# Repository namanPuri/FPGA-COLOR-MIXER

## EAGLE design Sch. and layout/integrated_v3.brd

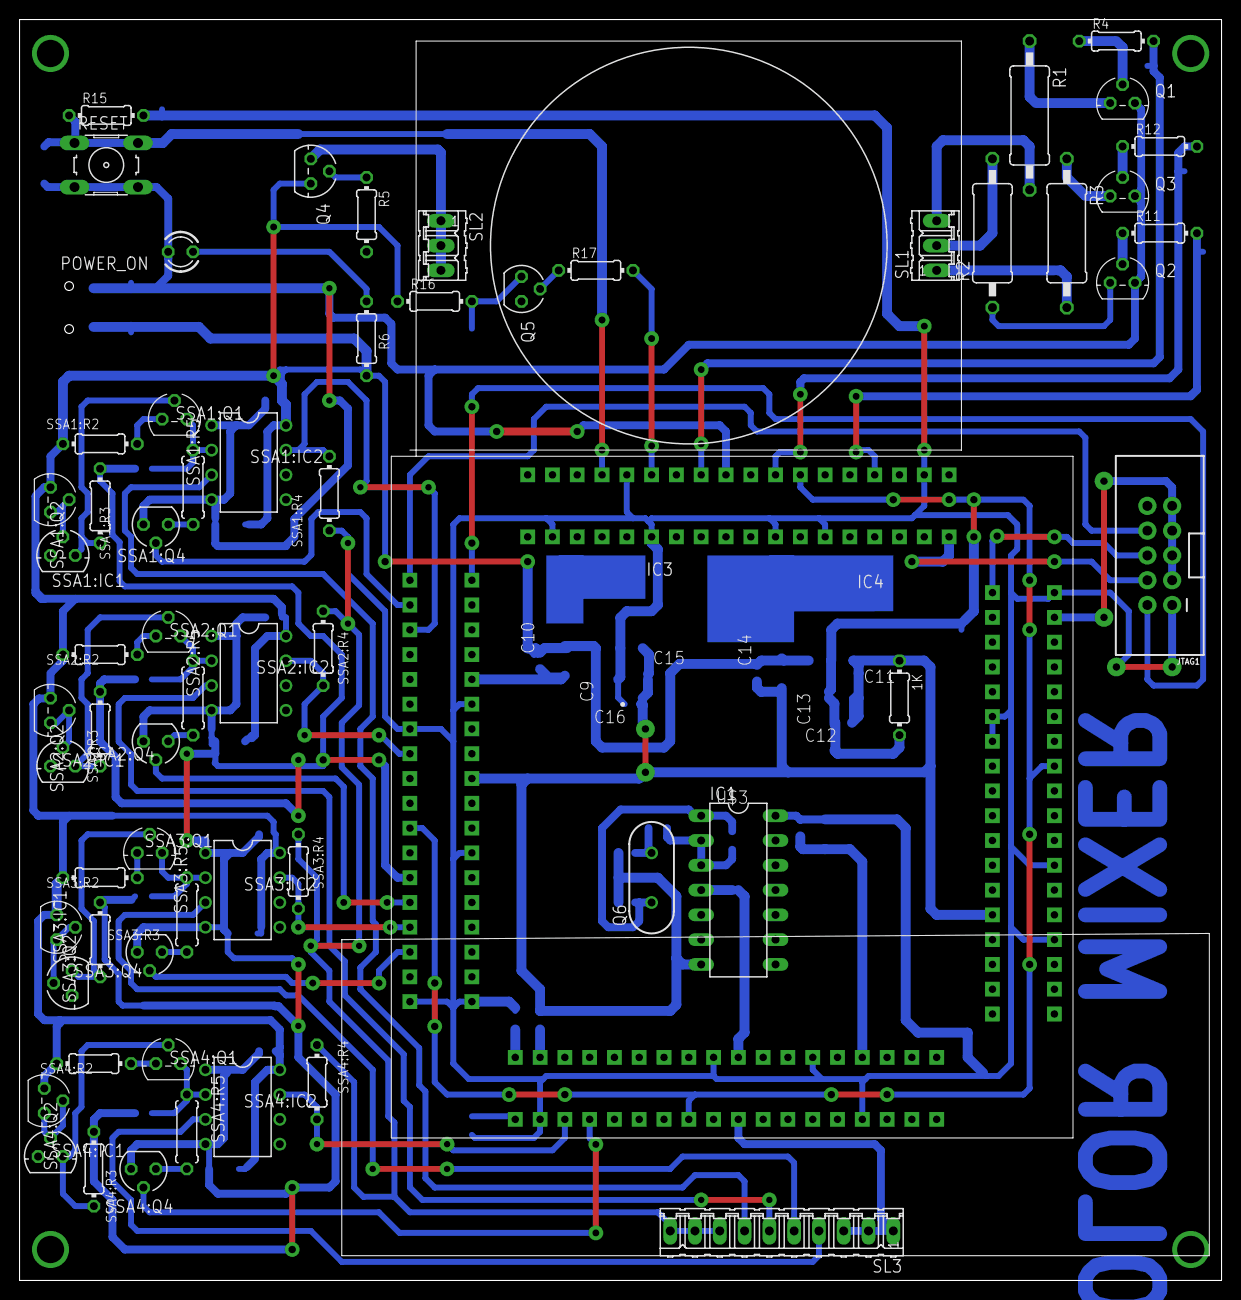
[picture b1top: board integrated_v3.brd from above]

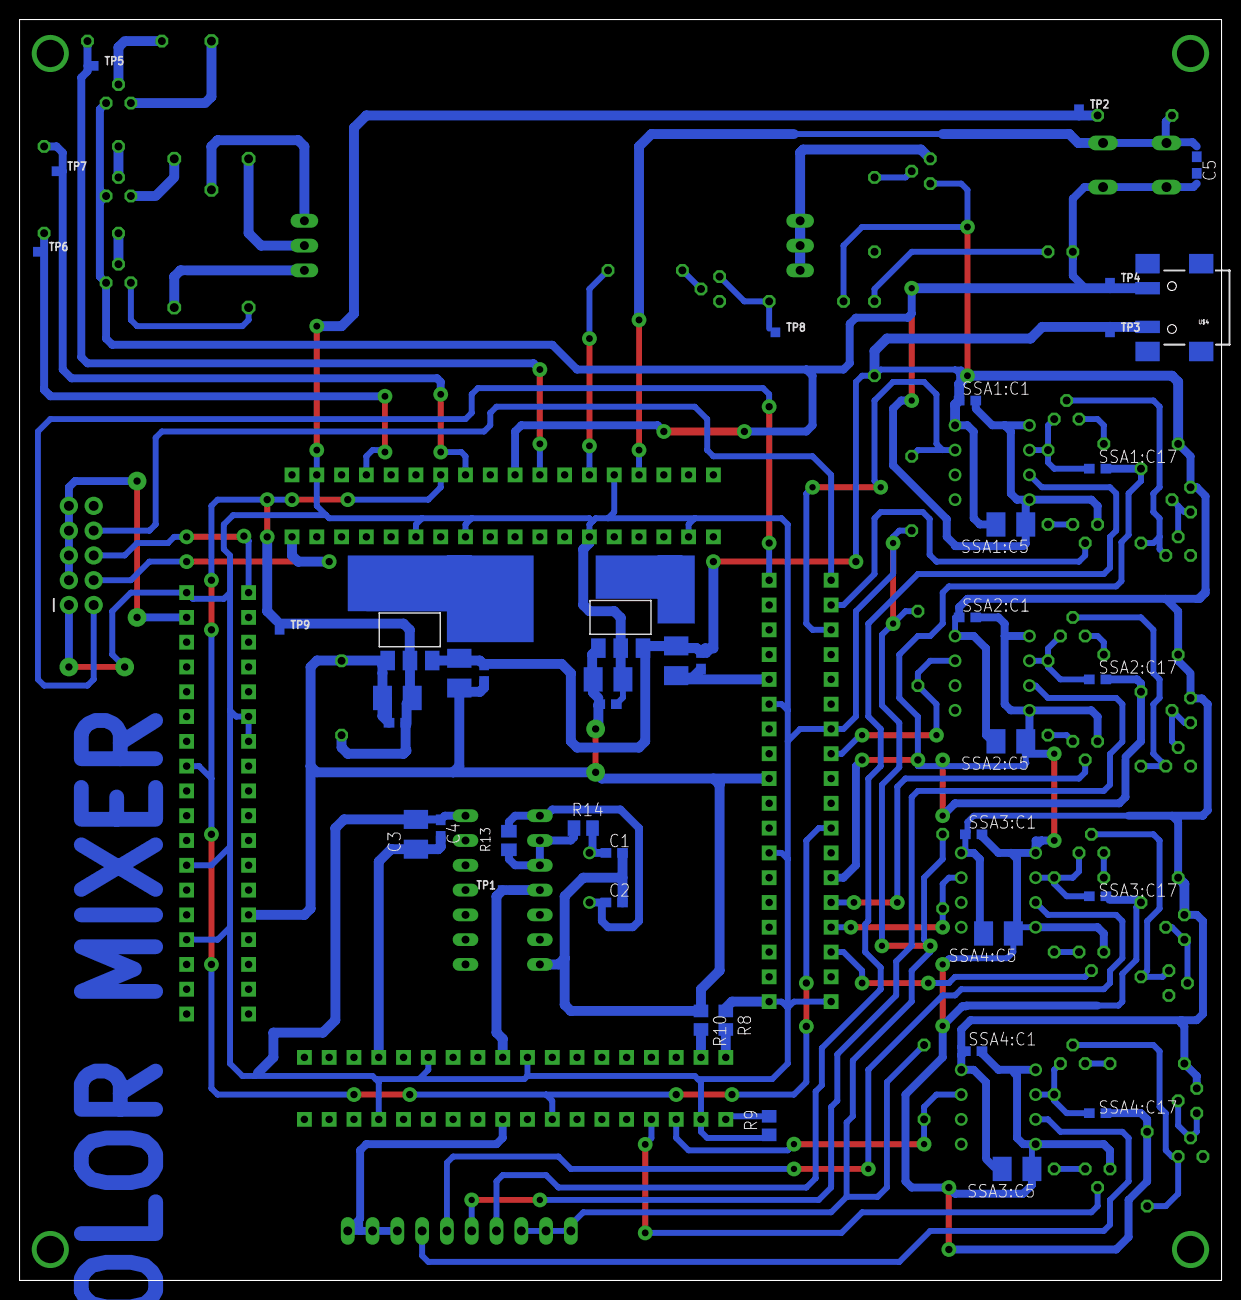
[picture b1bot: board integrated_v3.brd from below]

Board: 2 copper layers, 123.2 x 129.2 mm, 104 parts (42 on the bottom side), 66 nets.

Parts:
1K: 0204/7
C1: 22P; C0603
C2: 10P; C0603
C3, C9, C11, C13, C15: 10u; B/3528-21R
C4, C5, C10, C12, C14, C16: 0.1u; C0603
IC1: 74HC14N; DIL14
IC3, IC4: REG1117; SOT223
JTAG1: 2X5-SHROUDED_LOCK_PROPER
POWER_ON: LED3MM
Q1, Q2, Q3: BC337; TO92
Q4: BC327; TO92
Q5: BC547; SOT54A
Q6: 12MHZ; HC49US
R1, R2: 22; 0411/15
R3: 15; 0411/15
R4, R5, R11, R12, R17: 1k; 0204/7
R6: 4.7k; 0204/7
R8, R9, R10: 330; R0805
R13: 1M; M0805
R14: 100; M0805
R15: 330; 0204/7
R16: 10k; 0204/7
RESET: 10xx; B3F-10XX
SL1, SL2: 03P
SL3: 10P
SSA1:C1, SSA1:C17, SSA2:C1, SSA2:C17, SSA3:C1, SSA3:C17, SSA4:C1, SSA4:C17: 0.1u; C0603
SSA1:C5, SSA2:C5, SSA3:C5, SSA4:C5: 10u; B/3528-21R
SSA1:IC1, SSA2:IC1, SSA3:IC1, SSA4:IC1: LM336LP; TO92
SSA1:IC2, SSA2:IC2, SSA3:IC2, SSA4:IC2: LM311N; DIL08
SSA1:Q1, SSA1:Q2, SSA2:Q1, SSA2:Q2, SSA3:Q1, SSA3:Q2, SSA4:Q1, SSA4:Q2: BC557; TO92
SSA1:Q4, SSA2:Q4, SSA3:Q4, SSA4:Q4: BS170; SOT54E
SSA1:R2, SSA2:R2, SSA3:R2, SSA4:R2: 1.5k; 0204/7
SSA1:R3, SSA2:R3, SSA3:R3, SSA4:R3: 2k; 0204/7
SSA1:R4, SSA2:R4, SSA3:R4, SSA4:R4: 1k; 0204/7
SSA1:R5, SSA2:R5, SSA3:R5, SSA4:R5: 10; 0207/7
TP1, TP2, TP3, TP4, TP5, TP6, TP7, TP8, TP9: TESTPOINT_TPS-SMD-10SN; TESTPOINT_SMD-10SN
U$3: 144_BOB
U$4: USB(POWER)

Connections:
+1.2V: 1K.2, C11.+, C12.1, IC4.2, TP9.TP, U$3.22, U$3.52, U$3.94, U$3.122
+3V3: C3.+, C4.1, C15.+, C16.1, IC1.14, IC3.2, JTAG1.1, R8.1, R9.1, R15.2, SL3.8, SL3.9, SL3.10, SSA1:R4.2, SSA2:R4.2, SSA3:R4.2, SSA4:R4.2, TP2.TP, U$3.11, U$3.14, U$3.23, U$3.35, U$3.36, U$3.40, U$3.53, U$3.61, U$3.66, U$3.80, U$3.86, U$3.95, U$3.97, U$3.108, U$3.112, U$3.119, U$3.123, U$3.133, U$3.136, U$3.141
+5V: C9.+, C10.1, C13.+, C14.1, IC3.3, IC4.3, Q4.1, R6.2, R16.1, SSA1:C1.1, SSA1:C5.+, SSA1:IC2.8, SSA1:Q2.3, SSA1:R2.2, SSA2:C1.1, SSA2:C5.+, SSA2:IC2.8, SSA2:Q2.3, SSA2:R2.2, SSA3:C1.1, SSA3:C5.+, SSA3:IC2.8, SSA3:Q2.3, SSA3:R2.2, SSA4:C1.1, SSA4:C5.+, SSA4:IC2.8, SSA4:Q2.3, SSA4:R2.2, TP3.TP, U$4.VBUS
ADC_B: SSA3:IC2.7, SSA3:R4.1, U$3.30
ADC_G: SSA2:IC2.7, SSA2:R4.1, U$3.16
ADC_I: SSA4:IC2.7, SSA4:R4.1, U$3.42
ADC_R: SSA1:IC2.7, SSA1:R4.1, U$3.6
BLUE: R12.2, TP7.TP, U$3.124
CLK: IC1.4, TP1.TP, U$3.55
DIS_B: SSA3:Q4.G, U$3.32
DIS_G: SSA2:Q4.G, U$3.28
DIS_I: SSA4:Q4.G, U$3.44
DIS_R: SSA1:Q4.G, U$3.4
GND: 1K.1, C1.2, C2.2, C3.-, C4.2, C5.2, C9.-, C10.2, C11.-, C12.2, C13.-, C14.2, C15.-, C16.2, IC1.7, IC3.1, IC4.1, JTAG1.3, JTAG1.5, JTAG1.7, JTAG1.9, POWER_ON.K, Q1.1, Q2.1, Q3.1, Q5.E, R10.1, RESET.3, RESET.4, SL3.1, SL3.2, SL3.3, SSA1:C1.2, SSA1:C5.-, SSA1:C17.2, SSA1:IC2.1, SSA1:IC2.4, SSA1:Q4.S, SSA1:R3.1, SSA2:C1.2, SSA2:C5.-, SSA2:C17.2, SSA2:IC2.1, SSA2:IC2.4, SSA2:Q4.S, SSA2:R3.1, SSA3:C1.2, SSA3:C5.-, SSA3:C17.2, SSA3:IC2.1, SSA3:IC2.4, SSA3:Q4.S, SSA3:R3.1, SSA4:C1.2, SSA4:C5.-, SSA4:C17.2, SSA4:IC2.1, SSA4:IC2.4, SSA4:Q4.S, SSA4:R3.1, TP4.TP, U$3.9, U$3.17, U$3.26, U$3.34, U$3.56, U$3.65, U$3.81, U$3.89, U$3.100, U$3.106, U$3.118, U$3.128, U$3.137, U$4.GND
GREEN: R4.2, TP5.TP, U$3.130
INTENSITY: R17.2, U$3.134
INTENSITY5: Q5.C, R5.2, R16.2, TP8.TP
unnamed: Q1.3, R1.1
unnamed: R1.2, SL1.3
unnamed: Q2.3, R2.1
unnamed: C2.1, IC1.1, Q6.1, R13.2
unnamed: Q5.B, R17.1
unnamed: Q3.3, R3.1
unnamed: R3.2, SL1.1
unnamed: Q1.2, R4.1
unnamed: Q2.2, R11.1
unnamed: Q3.2, R12.1
unnamed: R2.2, SL1.2
unnamed: IC1.2, IC1.3, R13.1, R14.1
unnamed: C1.1, Q6.2, R14.2
unnamed: Q4.2, R5.1
unnamed: Q4.3, SL2.1, SL2.2, SL2.3
unnamed: POWER_ON.A, R6.1
unnamed: R8.2, U$3.37
unnamed: R9.2, U$3.38
unnamed: R10.2, U$3.39
POT_B: SL3.5, SSA3:IC2.3
POT_G: SL3.6, SSA2:IC2.3
POT_I: SL3.4, SSA4:IC2.3
POT_R: SL3.7, SSA1:IC2.3
RED: R11.2, TP6.TP, U$3.116
RESET: C5.1, R15.1, RESET.1, RESET.2, U$3.138
SSA1:COMP: SSA1:C17.1, SSA1:IC2.2, SSA1:Q1.1, SSA1:R5.2
SSA1:N$2: SSA1:Q1.3, SSA1:R2.1
SSA1:N$3: SSA1:IC1.2, SSA1:Q2.1, SSA1:Q2.2
SSA1:N$4: SSA1:IC1.3, SSA1:Q1.2, SSA1:R3.2
SSA1:N$5: SSA1:Q4.D, SSA1:R5.1
SSA2:COMP: SSA2:C17.1, SSA2:IC2.2, SSA2:Q1.1, SSA2:R5.2
SSA2:N$2: SSA2:Q1.3, SSA2:R2.1
SSA2:N$3: SSA2:IC1.2, SSA2:Q2.1, SSA2:Q2.2
SSA2:N$4: SSA2:IC1.3, SSA2:Q1.2, SSA2:R3.2
SSA2:N$5: SSA2:Q4.D, SSA2:R5.1
SSA3:COMP: SSA3:C17.1, SSA3:IC2.2, SSA3:Q1.1, SSA3:R5.2
SSA3:N$2: SSA3:Q1.3, SSA3:R2.1
SSA3:N$3: SSA3:IC1.2, SSA3:Q2.1, SSA3:Q2.2
SSA3:N$4: SSA3:IC1.3, SSA3:Q1.2, SSA3:R3.2
SSA3:N$5: SSA3:Q4.D, SSA3:R5.1
SSA4:COMP: SSA4:C17.1, SSA4:IC2.2, SSA4:Q1.1, SSA4:R5.2
SSA4:N$2: SSA4:Q1.3, SSA4:R2.1
SSA4:N$3: SSA4:IC1.2, SSA4:Q2.1, SSA4:Q2.2
SSA4:N$4: SSA4:IC1.3, SSA4:Q1.2, SSA4:R3.2
SSA4:N$5: SSA4:Q4.D, SSA4:R5.1
TCK: JTAG1.4, U$3.109
TDI: JTAG1.8, U$3.2
TDO: JTAG1.6, U$3.107
TMS: JTAG1.2, U$3.1

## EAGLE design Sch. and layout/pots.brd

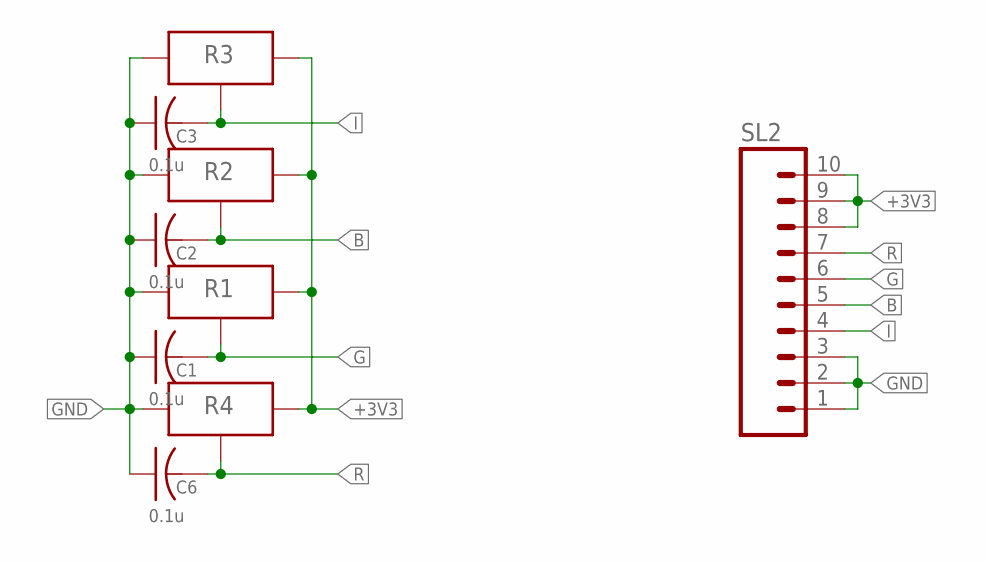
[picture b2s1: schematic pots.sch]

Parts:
C1, C2, C3, C6: 0.1u; C0603
R1, R2, R3, R4: POTNORMAL; RJ9W
SL2: M10; 10P

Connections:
+3V3: R1.A, R2.A, R3.A, R4.A, SL2.8, SL2.9, SL2.10
B: C2.2, R2.S, SL2.5
G: C1.2, R1.S, SL2.6
GND: C1.1, C2.1, C3.1, C6.1, R1.E, R2.E, R3.E, R4.E, SL2.1, SL2.2, SL2.3
I: C3.2, R3.S, SL2.4
R: C6.2, R4.S, SL2.7

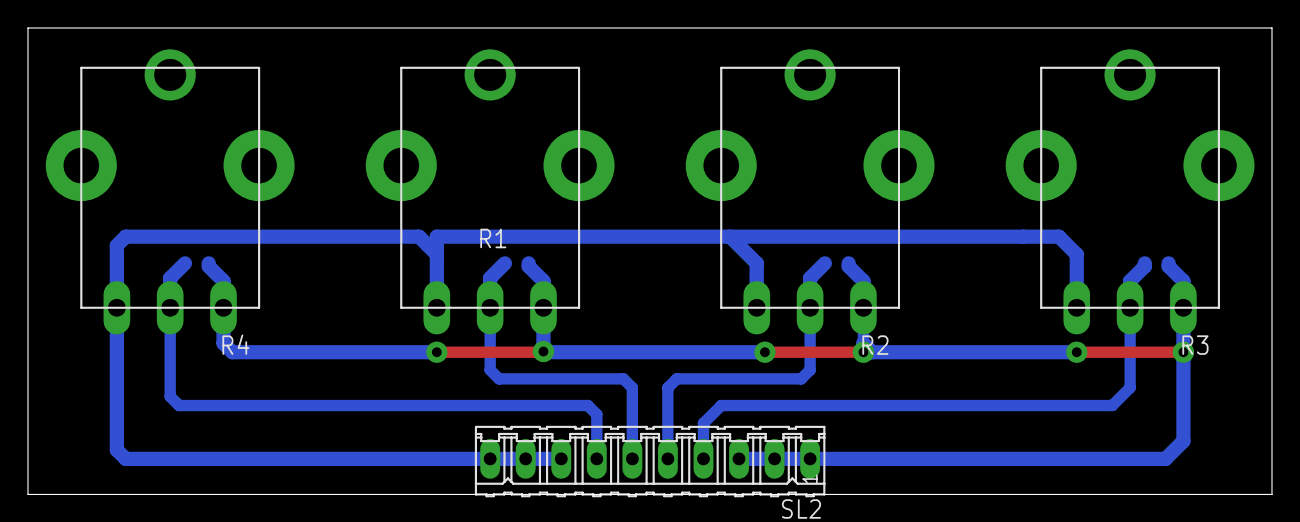
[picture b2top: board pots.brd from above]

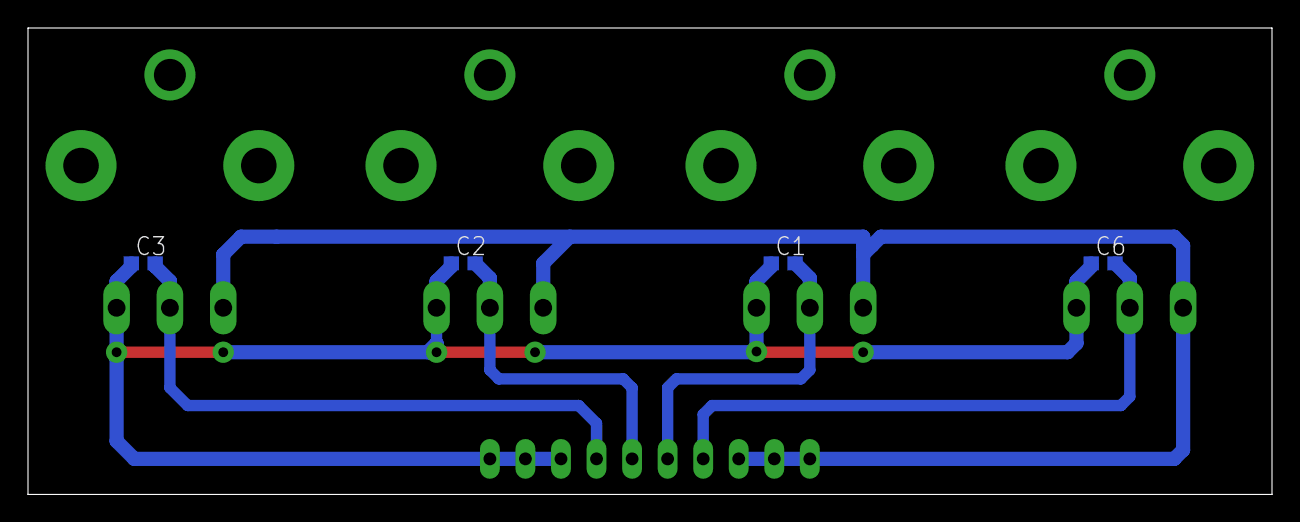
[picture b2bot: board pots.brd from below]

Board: 2 copper layers, 88.9 x 33.3 mm, 9 parts (4 on the bottom side), 6 nets.

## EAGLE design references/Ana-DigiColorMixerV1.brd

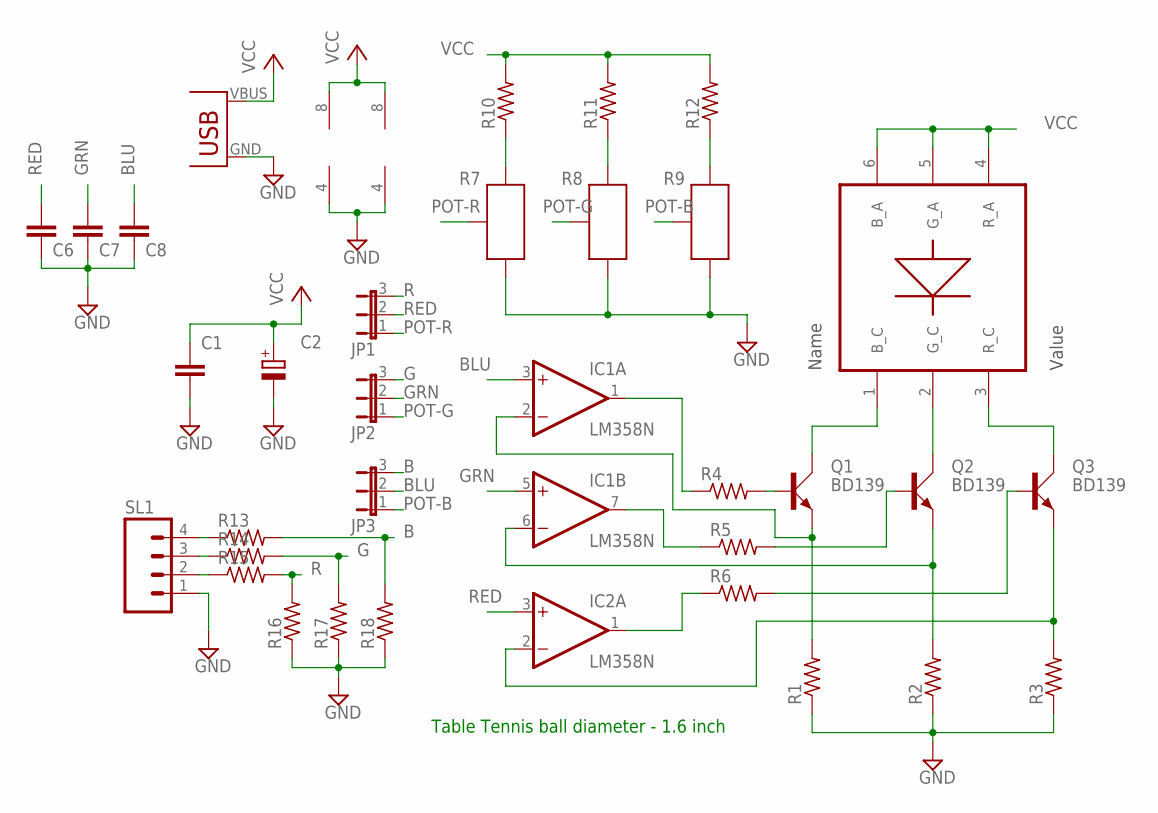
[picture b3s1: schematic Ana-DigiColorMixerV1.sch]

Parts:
C1, C6, C7, C8: 0.1uf; C025-024X044
C2: 100uf; E3,5-8
IC1, IC2: LM358N; DIL08
JP1, JP2, JP3: JP2E; JP2
Q1, Q2, Q3: BD139; TO126AV
R1: 4.7; 0411/15
R2, R3: R-US_0411/15; 0411/15
R4, R5, R6, R10, R11, R12, R13, R14, R15, R16, R17, R18: R-US_0204/7; 0204/7
R7, R8, R9: POTNORMAL; RJ9W
SL1: M04; 04P
U$1: RGB_SMD_3W; RGB_SMD_6PIN
U$2: USB(POWER)

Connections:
3V3: R9.E, R12.1
B: JP3.3, R13.2, R18.2
BLU: C8.1, IC1.3 (+IN), JP3.2
G: JP2.3, R14.2, R17.2
GND: C1.2, C2.-, C6.2, C7.2, C8.2, IC1.4 (V-), IC2.4 (V-), R1.1, R2.1, R3.1, R7.A, R8.A, R9.A, R16.1, R17.1, R18.1, SL1.1, U$2.GND
GRN: C7.1, IC1.5 (+IN), JP2.2
unnamed: Q1.C, U$1.1 (B_C)
unnamed: Q2.C, U$1.2 (G_C)
unnamed: Q3.C, U$1.3 (R_C)
unnamed: Q1.B, R4.2
unnamed: Q2.B, R5.2
unnamed: Q3.B, R6.2
unnamed: IC1.6 (-IN), Q2.E, R2.2
unnamed: R13.1, SL1.4
unnamed: IC1.1 (OUT), R4.1
unnamed: IC1.7 (OUT), R5.1
unnamed: IC2.1 (OUT), R6.1
unnamed: R14.1, SL1.3
unnamed: R15.1, SL1.2
unnamed: R7.E, R10.1
unnamed: R8.E, R11.1
unnamed: IC1.2 (-IN), Q1.E, R1.2
unnamed: IC2.2 (-IN), Q3.E, R3.2
POT-B: JP3.1, R9.S
POT-G: JP2.1, R8.S
POT-R: JP1.1, R7.S
R: JP1.3, R15.2, R16.2
RED: C6.1, IC2.3 (+IN), JP1.2
VCC: C1.1, C2.+, IC1.8 (V+), IC2.8 (V+), R10.2, R11.2, R12.2, U$1.4 (R_A), U$1.5 (G_A), U$1.6 (B_A), U$2.VBUS (VCC)

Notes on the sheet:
Table Tennis ball diameter - 1.6 inch

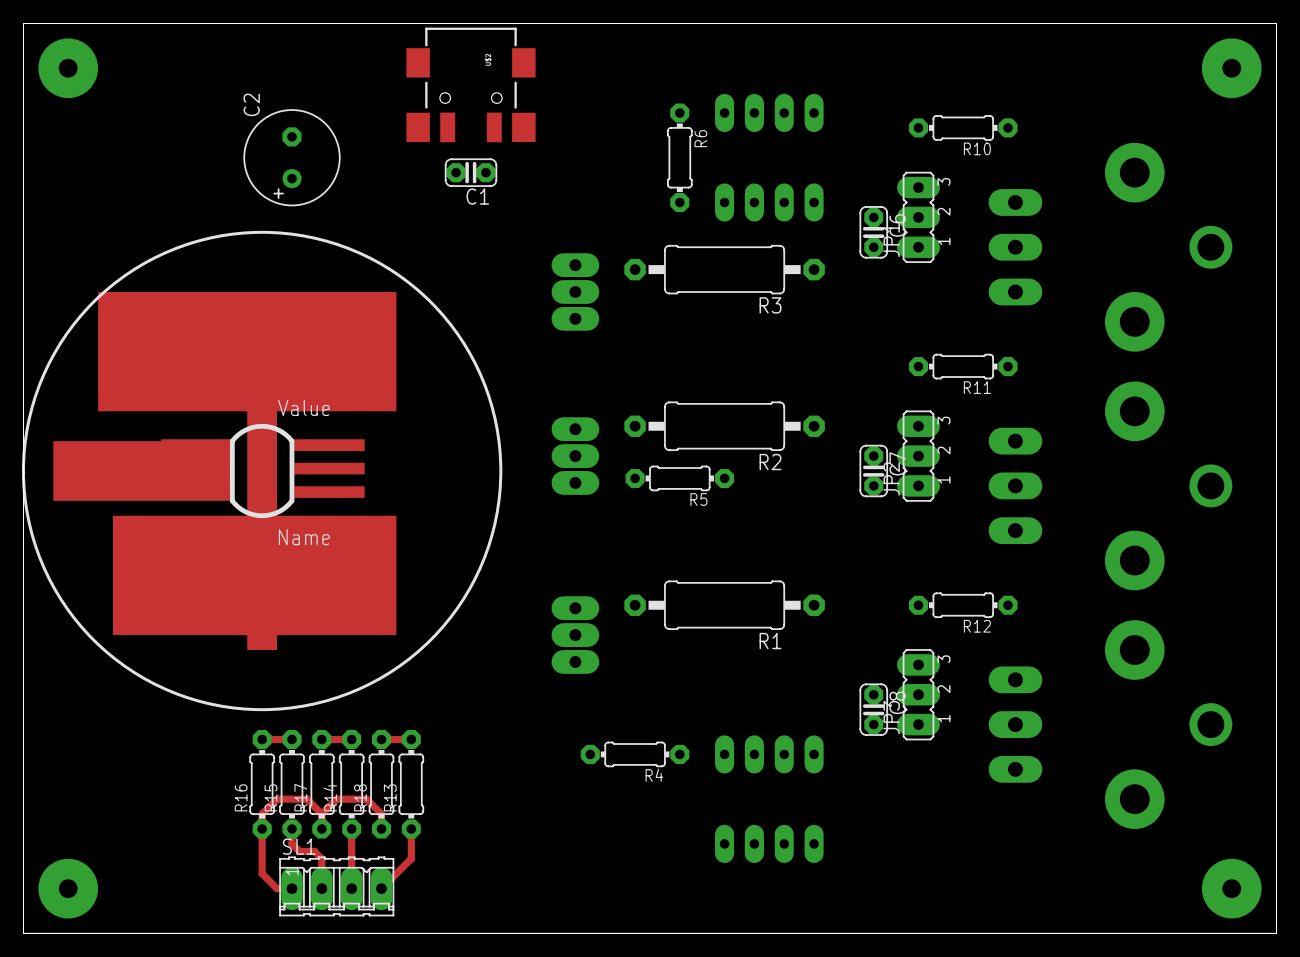
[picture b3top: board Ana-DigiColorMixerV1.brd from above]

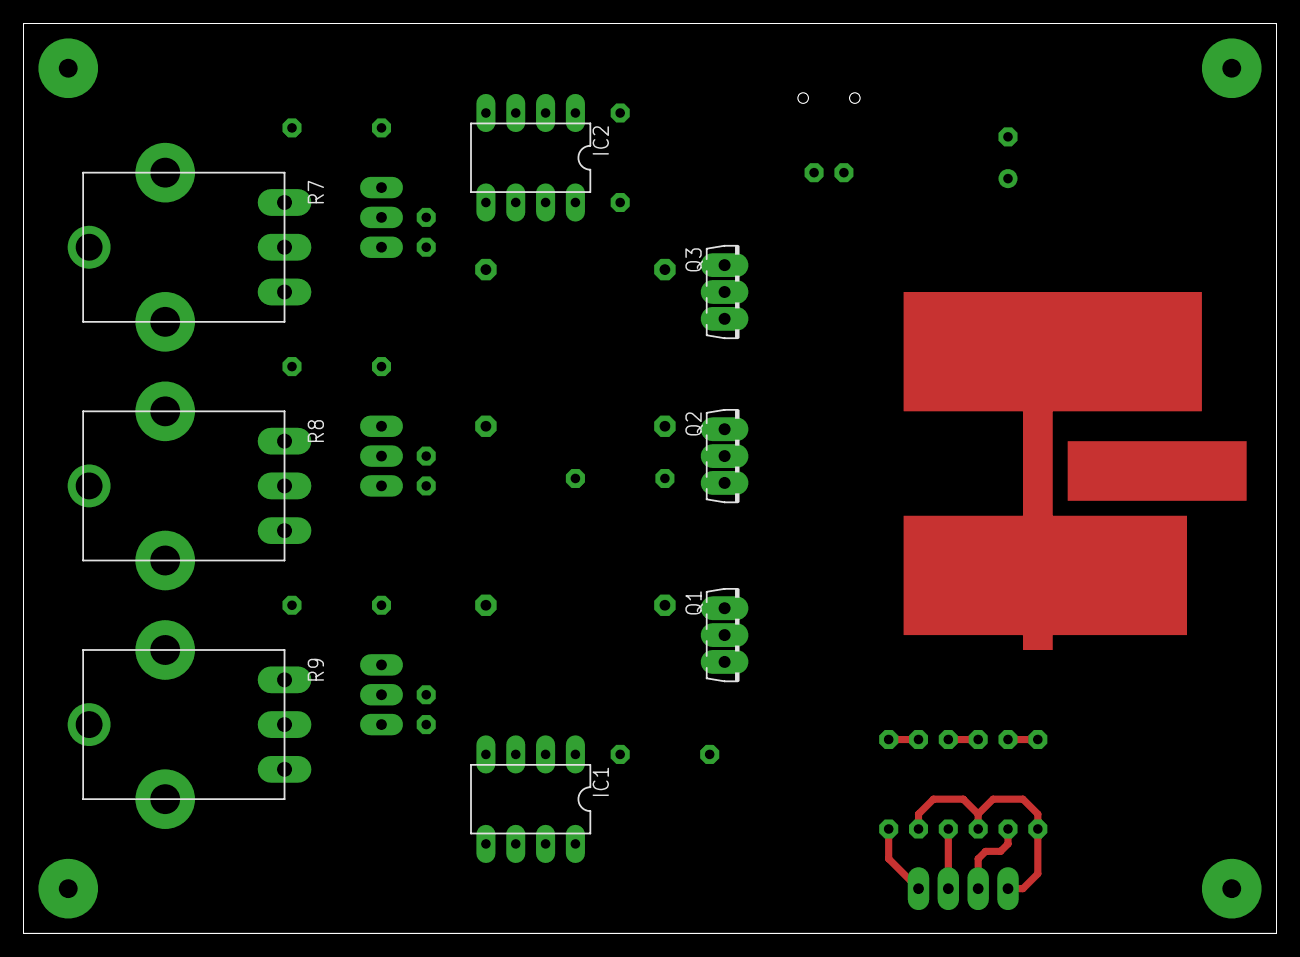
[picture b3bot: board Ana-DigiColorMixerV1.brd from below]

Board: 2 copper layers, 106.7 x 77.5 mm, 34 parts (8 on the bottom side), 29 nets.

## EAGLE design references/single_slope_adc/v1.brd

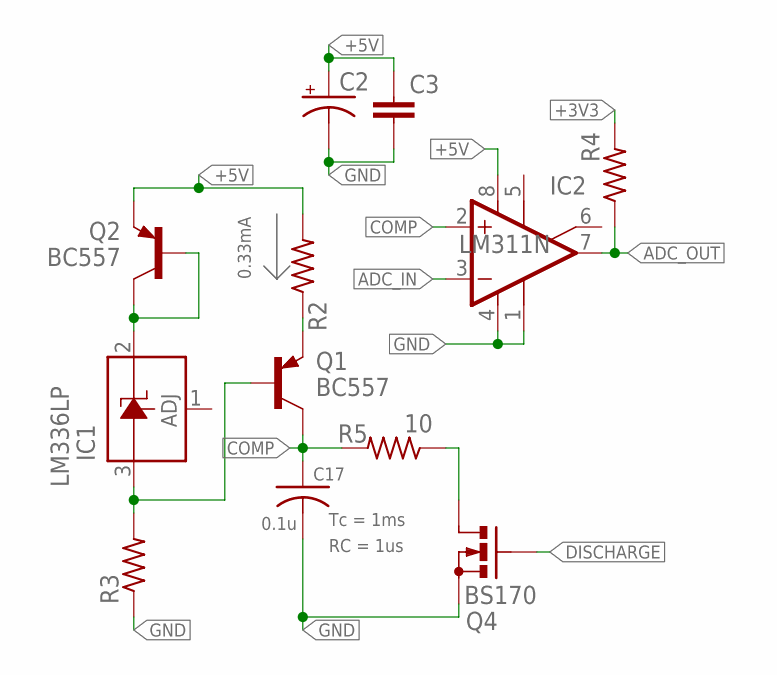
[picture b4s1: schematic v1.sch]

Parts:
C2: CPOL-USE2.5-5; E2,5-5
C3: C-EU025-024X044; C025-024X044
C17: 0.1u; C0603
IC1: LM336LP; TO92
IC2: LM311N; DIL08
Q1, Q2: BC557; TO92
Q4: BS170; SOT54E
R2, R3, R4: R-US_0204/7; 0204/7
R5: 10; 0207/7

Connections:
+3V3: R4.2
+5V: C2.+, C3.1, IC2.8 (V+), Q2.3 (E), R2.2
ADC_IN: IC2.3 (-IN)
ADC_OUT: IC2.7 (OUT), R4.1
COMP: C17.1, IC2.2 (+IN), Q1.1 (C), R5.2
DISCHARGE: Q4.G
GND: C2.-, C3.2, C17.2, IC2.1 (GND), IC2.4 (V-), Q4.S, R3.1
unnamed: Q1.3 (E), R2.1
unnamed: IC1.2 (C), Q2.1 (C), Q2.2 (B)
unnamed: IC1.3 (A), Q1.2 (B), R3.2
unnamed: Q4.D, R5.1

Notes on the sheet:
0.33mA
Tc = 1ms
RC = 1us

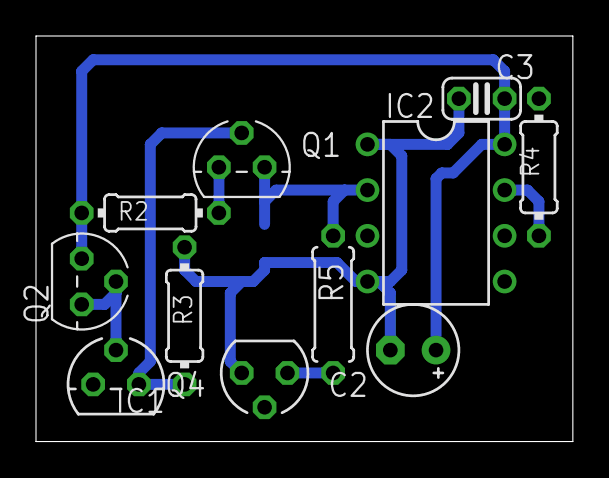
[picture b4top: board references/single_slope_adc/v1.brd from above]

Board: 2 copper layers, 29.8 x 22.5 mm, 12 parts (1 on the bottom side), 8 nets.

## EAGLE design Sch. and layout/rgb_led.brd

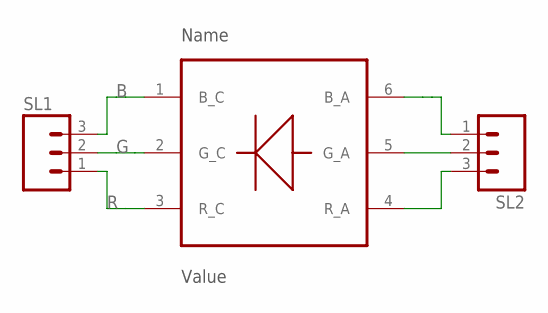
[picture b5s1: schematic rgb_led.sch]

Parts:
SL1, SL2: M03; 03P
U$2: RGB_SMD_3W; RGB_SMD_6PIN

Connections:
B: SL1.3, U$2.1 (B_C)
G: SL1.2, U$2.2 (G_C)
unnamed: SL2.1, U$2.6 (B_A)
unnamed: SL2.2, U$2.5 (G_A)
unnamed: SL2.3, U$2.4 (R_A)
R: SL1.1, U$2.3 (R_C)

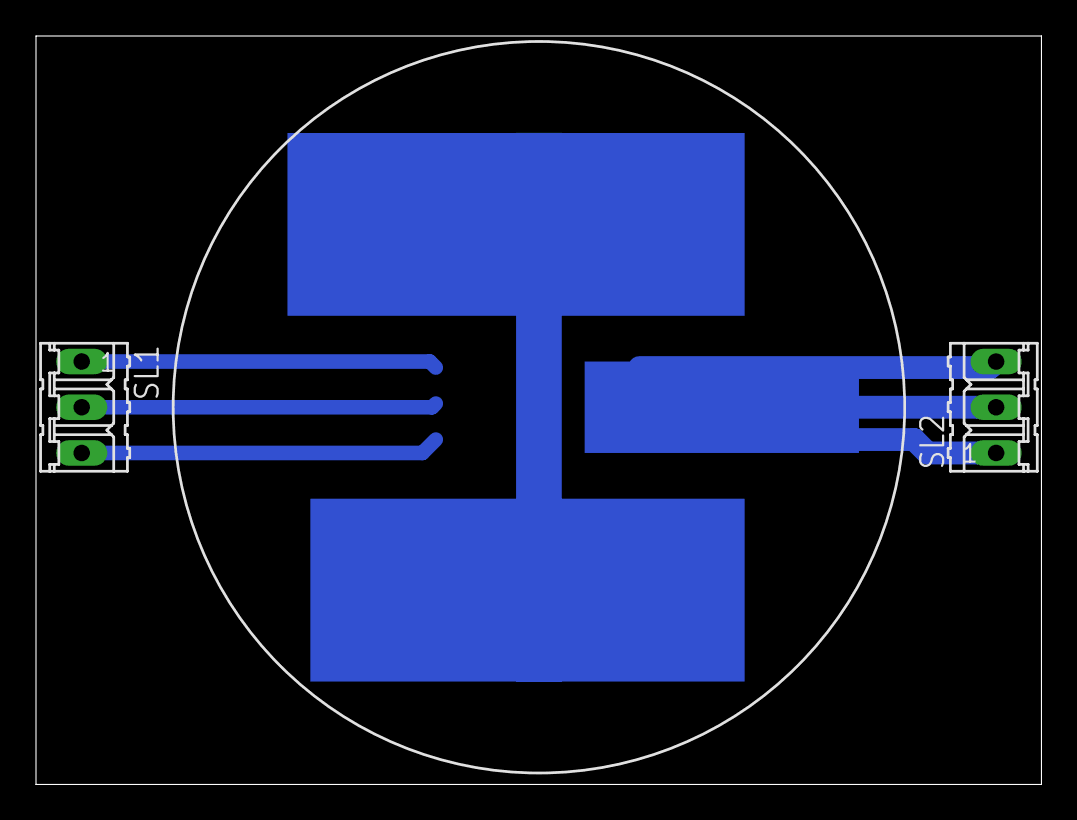
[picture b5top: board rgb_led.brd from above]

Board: 2 copper layers, 55.9 x 41.6 mm, 3 parts (1 on the bottom side), 6 nets.

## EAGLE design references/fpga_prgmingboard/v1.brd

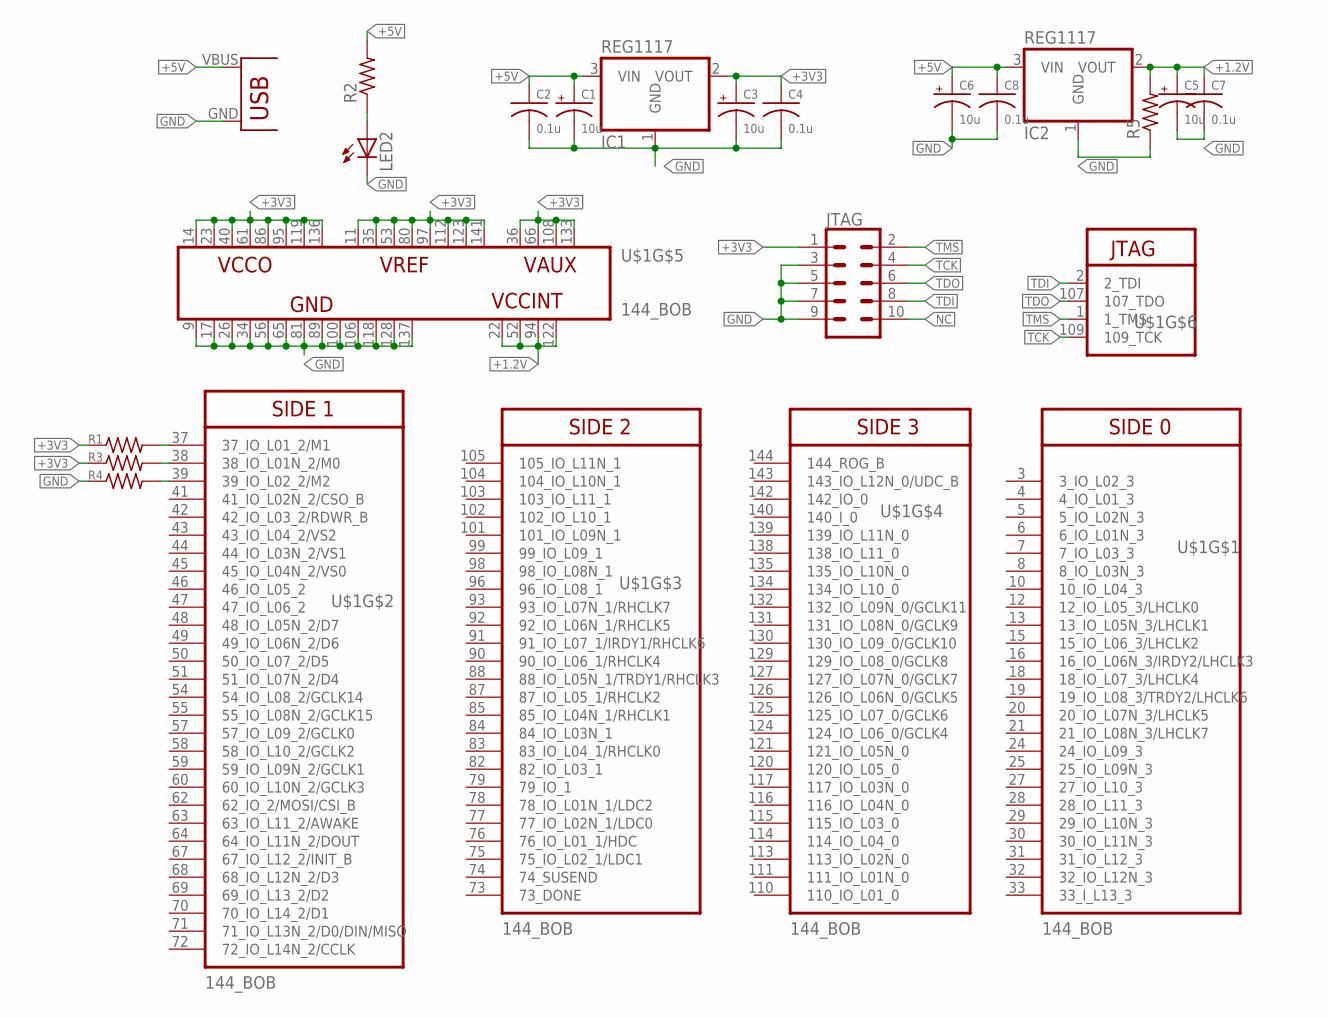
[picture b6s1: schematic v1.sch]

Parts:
C1, C3, C5, C6: 10u; B/3528-21R
C2, C4, C7, C8: 0.1u; C0603
IC1, IC2: REG1117; SOT223
JTAG: CONN_05X2; 2X5-SHROUDED_LOCK_PROPER
LED2: LED3MM
R1, R3, R4: RESISTOR0805; R0805
R2, R5: R-US_0204/7; 0204/7
U$1: 144_BOB
U$2: USB(POWER)

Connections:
+1.2V: C5.+, C7.1, IC2.2 (VOUT), R5.2, U$1.22 (22_VCCINT), U$1.52 (52_VCCINT), U$1.94 (94_VCCINT), U$1.122 (122_VCCINT)
+3V3: C3.+, C4.1, IC1.2 (VOUT), JTAG.1, R1.1, R3.1, U$1.11 (11_VREF), U$1.14 (14_VCCO), U$1.23 (23_VCCO), U$1.35 (35_VREF), U$1.36 (36_VAUX), U$1.40 (40_VCCO), U$1.53 (53_VREF), U$1.61 (61_VCCO), U$1.66 (66_VAUX), U$1.80 (80_VREF), U$1.86 (86_VCCO), U$1.95 (95_VCCO), U$1.97 (97_VREF), U$1.108 (108_VAUX), U$1.112 (112_VREF), U$1.119 (119_VCCO), U$1.123 (123_VREF), U$1.133 (133_VAUX), U$1.136 (136_VCCO), U$1.141 (141_VREF)
+5V: C1.+, C2.1, C6.+, C8.1, IC1.3 (VIN), IC2.3 (VIN), R2.2, U$2.VBUS (VCC)
GND: C1.-, C2.2, C3.-, C4.2, C5.-, C6.-, C7.2, C8.2, IC1.1 (GND), IC2.1 (GND), JTAG.3, JTAG.5, JTAG.7, JTAG.9, LED2.K (C), R4.1, R5.1, U$1.9 (9_GND), U$1.17 (17_GND), U$1.26 (26_GND), U$1.34 (34_GND), U$1.56 (56_GND), U$1.65 (65_GND), U$1.81 (81_GND), U$1.89 (89_GND), U$1.100 (100_GND), U$1.106 (106_GND), U$1.118 (118_GND), U$1.128 (128_GND), U$1.137 (137_GND), U$2.GND
unnamed: R1.2, U$1.37 (37_IO_L01_2/M1)
unnamed: LED2.A, R2.1
unnamed: R3.2, U$1.38 (38_IO_L01N_2/M0)
unnamed: R4.2, U$1.39 (39_IO_L02_2/M2)
NC: JTAG.10
TCK: JTAG.4, U$1.109 (109_TCK)
TDI: JTAG.8, U$1.2 (2_TDI)
TDO: JTAG.6, U$1.107 (107_TDO)
TMS: JTAG.2, U$1.1 (1_TMS)

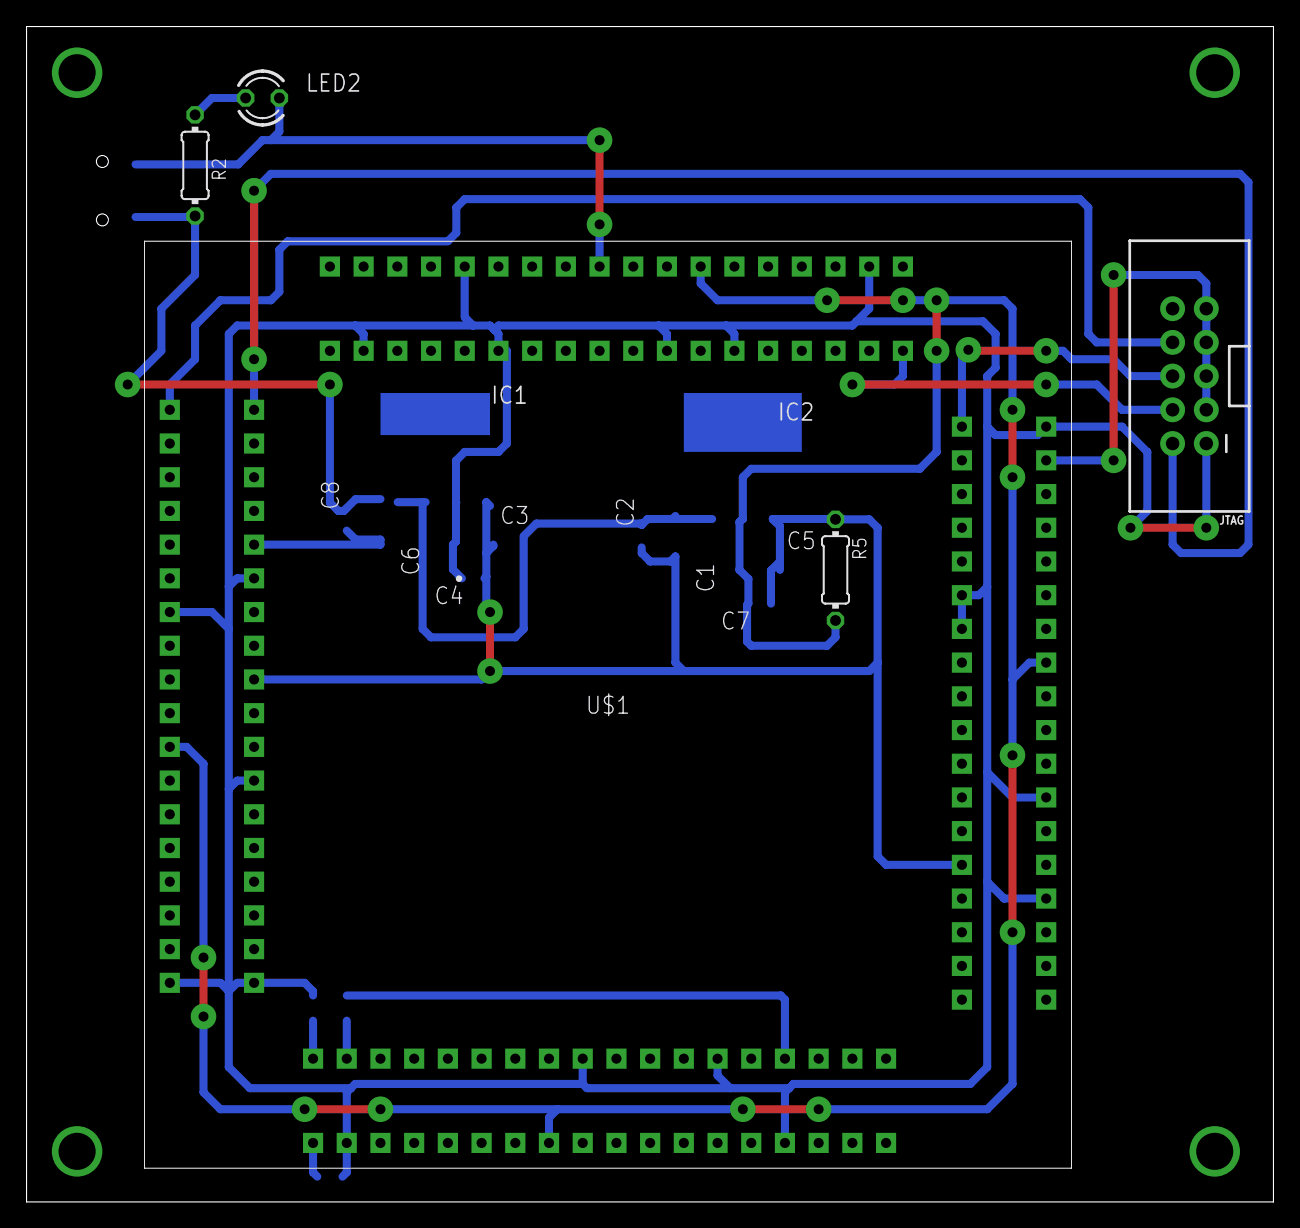
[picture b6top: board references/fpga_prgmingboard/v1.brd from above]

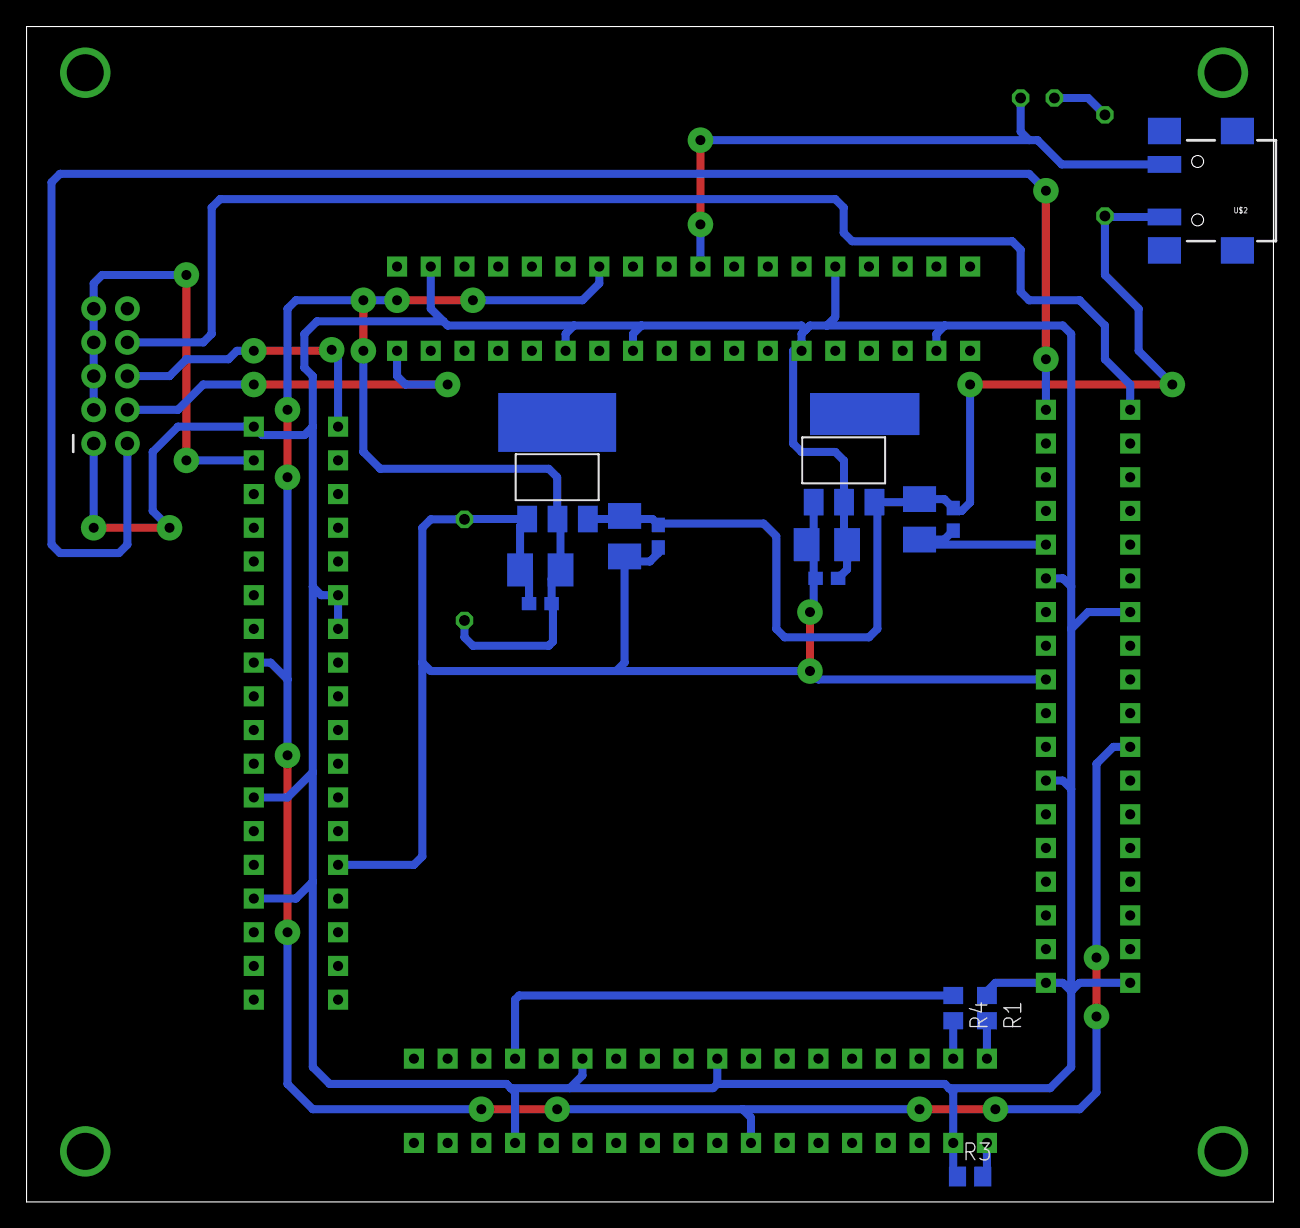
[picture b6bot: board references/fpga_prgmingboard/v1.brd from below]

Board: 2 copper layers, 94.0 x 88.6 mm, 19 parts (14 on the bottom side), 12 nets.

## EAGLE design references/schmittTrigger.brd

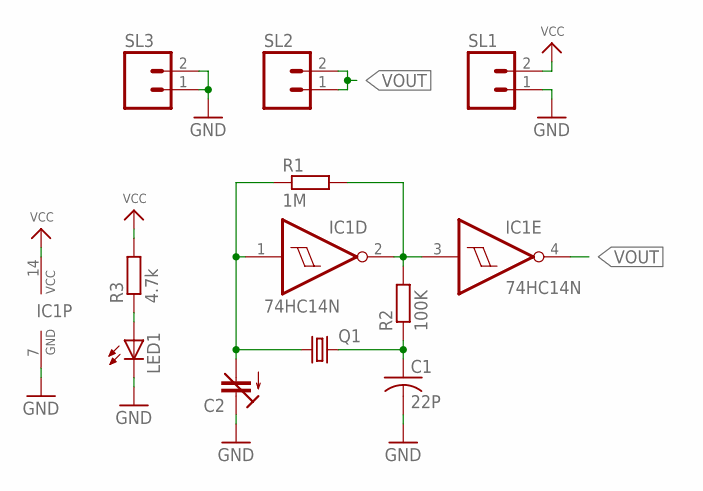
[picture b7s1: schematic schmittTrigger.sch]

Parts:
C1: 22P; C025-024X044
C2: C-TRIMM808; CTRIM808-BC
IC1: 74HC14N; DIL14
LED1: LED3MM
Q1: CRYSTALTC26H; TC26H
R1: 1M; 0204/5
R2: 100K; 0204/5
R3: 4.7k; 0204/5
SL1, SL2, SL3: M02; 02P

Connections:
GND: C1.2, C2.1 (E), IC1.7 (GND), LED1.K (C), SL1.1, SL3.1, SL3.2
unnamed: C2.2 (A), IC1.1 (I), Q1.1, R1.1
unnamed: IC1.2 (O), IC1.3 (I), R1.2, R2.2
unnamed: C1.1, Q1.2, R2.1
unnamed: LED1.A, R3.1
VCC: IC1.14 (VCC), R3.2, SL1.2
VOUT: IC1.4 (O), SL2.1, SL2.2

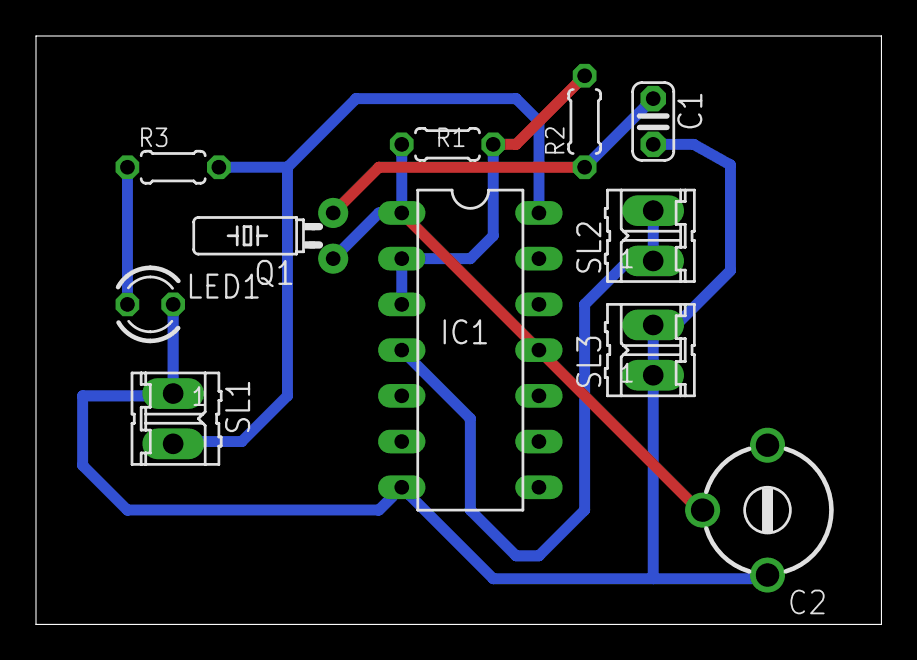
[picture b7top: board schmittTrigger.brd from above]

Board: 2 copper layers, 47.0 x 32.7 mm, 11 parts (0 on the bottom side), 7 nets.

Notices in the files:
parts and their libraries:
SparkFun-Connectors_v3: Licensing: Creative Commons ShareAlike 4.0 International - https://creativecommons.org/licenses/by-sa/4.0
